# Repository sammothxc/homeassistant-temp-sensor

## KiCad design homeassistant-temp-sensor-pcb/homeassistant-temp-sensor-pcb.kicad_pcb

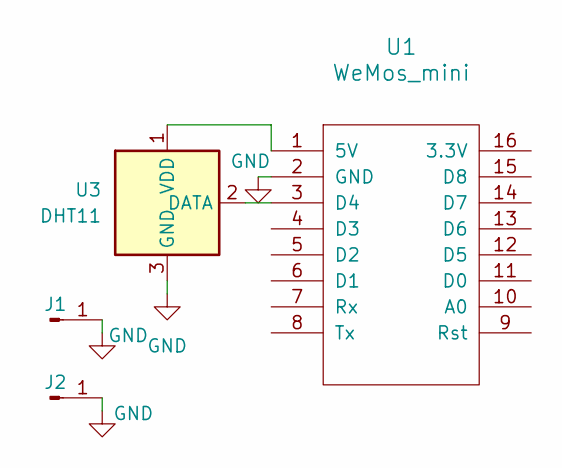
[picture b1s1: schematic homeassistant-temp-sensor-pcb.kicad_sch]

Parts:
J1, J2: Conn_01x01_Pin; PinHeader_1x01_P2.54mm_Vertical
U1: WeMos_mini; D1_mini_board
U3: DHT11; PinHeader_1x03_P2.54mm_Vertical

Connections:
GND: J1.1 (Pin_1_1), J2.1 (Pin_1_1), U1.2 (GND), U3.3 (GND)
unnamed: U1.1 (5V), U3.1 (VDD)
unnamed: U1.3 (D4), U3.2 (DATA)

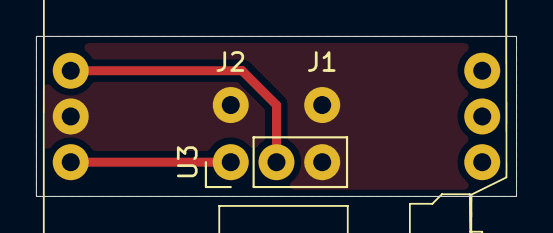
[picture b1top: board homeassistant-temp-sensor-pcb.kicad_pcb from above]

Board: 2 copper layers, 26.7 x 8.9 mm, 4 parts (0 on the bottom side), 3 nets.

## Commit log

2025-11-08 initial pcb commits
2025-11-08 schematic
2025-11-08 more pcb
2025-11-09 final kicad stuff
